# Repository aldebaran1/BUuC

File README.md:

This repo holds files for BU Arduino

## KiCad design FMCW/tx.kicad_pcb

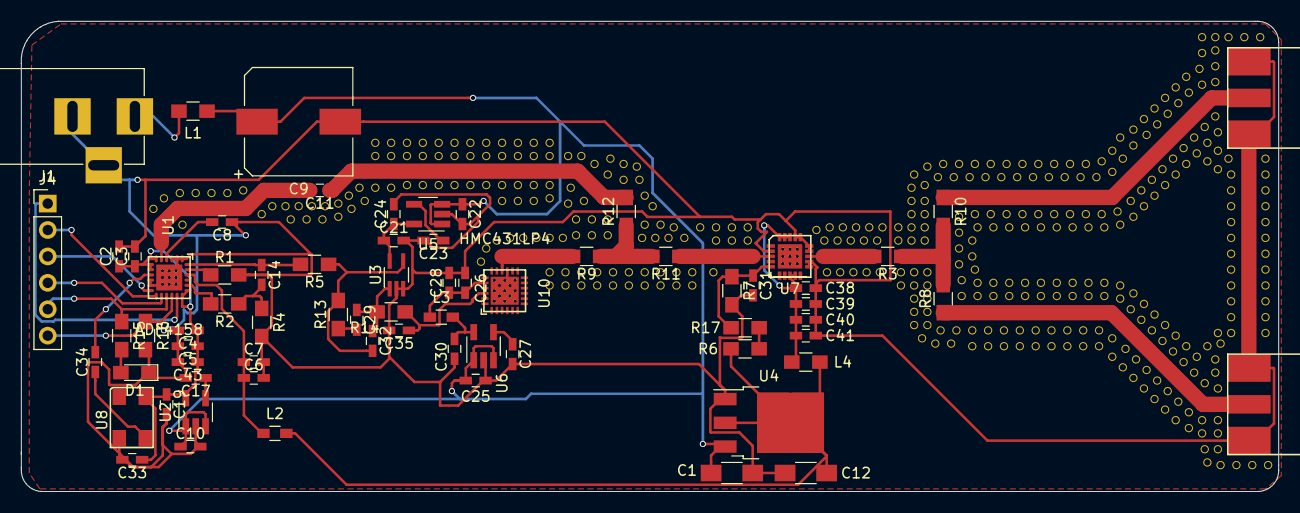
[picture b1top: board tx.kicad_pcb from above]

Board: 2 copper layers, 120.9 x 45.2 mm, 70 parts (0 on the bottom side), 42 nets.

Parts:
C1: 10u; C_1206_HandSoldering
C2, C4, C6, C21, C33, C34, C43: 100n; C_0603_HandSoldering
C3, C5, C7: 10p; C_0603_HandSoldering
C8, C11, C40, C41: 100p; C_0603_HandSoldering
C9: 470u; CP_Elec_10x10
C10, C22, C25: 1u; C_0603_HandSoldering
C12: 100u; C_1206_HandSoldering
C14: 47p; C_0603_HandSoldering
C17, C23, C27, C28, C31: 10n; C_0603_HandSoldering
C19, C26, C30: 4.7u; C_0603_HandSoldering
C24, C39: 2.2u; C_0603_HandSoldering
C29: 20n; C_0603_HandSoldering
C32: 750p; C_0603_HandSoldering
C35: 56n; C_0603_HandSoldering
C38: 10u; C_0603_HandSoldering
D1: LED; LED_0805_HandSoldering
J1: Barrel_Jack; BARREL_JACK
J2: SMA_RX; SMA_molex_straight
J3: SMA_TX; SMA_molex_straight
J4: Conn_01x06_Male; Pin_Header_Straight_1x06_Pitch2.54mm
L1, L4: CIC21P101NE; L_0805_HandSoldering
L2, L3: BLM18PG181SN1D; L_0603_HandSoldering
R1, R7: 5.1k; R_0805_HandSoldering
R2: 1.02k; R_0805_HandSoldering
R3, R8, R9, R10, R11, R12: 16; R_0805_HandSoldering
R4: 3.1k; R_0805_HandSoldering
R5, R15: 1k; R_0805_HandSoldering
R6: 3.3k; R_0805_HandSoldering
R13: 220; R_0805_HandSoldering
R14: 10; R_0805_HandSoldering
R16: 10k; R_0805_HandSoldering
R17: 510; R_0805_HandSoldering
U1: ADF4158; VFQFN-24
U2: LP2985-3.3; SOT-23-5_HandSoldering
U3: TLV172DCK; SOT-353_SC-70-5_Handsoldering
U4: LM1117-5.0; TO-252-3_TabPin2
U5: LP2985-10.0; SOT-23-5_HandSoldering
U6: LP2985-3.0; SOT-23-5_HandSoldering
U7: SE5003_1; SE5003
U8: TCXO
U10: HMC431LP4; VQFN-24

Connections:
/3V0: C30.1, L3.2, U6.5
/3V3: C2.1, C3.1, C4.1, C5.1, C19.1, C33.1, C43.1, U1.6, U1.7, U1.8, U1.18, U1.19, U2.5, U8.4
/5V: C12.1, L2.2, L4.2, R6.2, U4.2
/10V: C21.1, C24.1, U3.5, U5.5
/12V: C1.1, C9.1, C10.1, C22.1, C25.1, L1.1, U2.1, U2.3, U4.3, U5.1, U5.3, U6.1, U6.3
GND: C1.2, C2.2, C3.2, C4.2, C5.2, C6.2, C7.2, C8.1, C9.2, C10.2, C12.2, C17.2, C19.2, C21.2, C22.2, C23.2, C24.2, C25.2, C26.2, C27.2, C28.2, C30.2, C31.2, C33.2, C35.2, C38.1, C39.1, C40.1, C41.1, C43.2, D1.1, J1.2, J1.3, J2.2, J3.2, R1.2, R4.2, R7.2, R16.2, U1.1, U1.2, U1.3, U1.10, U1.11, U1.PAD, U2.2, U3.2, U3.3, U4.1, U5.2, U6.2, U7.2, U7.4, U7.11, U7.12, U7.14, U7.15, U7.16, U7.17, U7.GND, U7.PAD, U8.2, U10.15, U10.PAD
unnamed: C6.1, C7.1, L2.1, U1.22
unnamed: C8.2, U1.4
unnamed: C11.1, R12.2
unnamed: C11.2, U1.5
unnamed: C14.1, R5.2, U1.24
unnamed: C14.2, R2.1, R4.1
unnamed: C17.1, U2.4
unnamed: C23.1, U5.4
unnamed: C26.1, C28.1, L3.1, U10.20
unnamed: C27.1, U6.4
unnamed: C29.1, C32.1, R14.2, U3.1
unnamed: C29.2, R13.1
unnamed: C31.1, R7.1, R17.1, U7.5
unnamed: C32.2, R5.1, R13.2, U3.4
unnamed: C34.1, U8.3
unnamed: C34.2, U1.9
unnamed: C35.1, R14.1, U10.22
unnamed: C38.2, C39.2, C40.2, C41.2, L4.1, U7.8, U7.9, U7.18, U7.19, U7.20
unnamed: D1.2, R15.2
unnamed: J1.1, L1.2
unnamed: J2.1, R10.1
unnamed: J3.1, R8.1
unnamed: J4.1, U1.17
unnamed: J4.2, U1.13
unnamed: J4.3, U1.12
unnamed: J4.4, U1.14
unnamed: J4.5, R15.1, U1.15
unnamed: J4.6, R16.1, U1.16
unnamed: R1.1, U1.23
unnamed: R2.2, U1.20
unnamed: R3.2, U7.13
unnamed: R9.2, U10.16
unnamed: R3.1, R8.2, R10.2
unnamed: R11.1, U7.3
unnamed: R9.1, R11.2, R12.1
unnamed: R6.1, R17.2

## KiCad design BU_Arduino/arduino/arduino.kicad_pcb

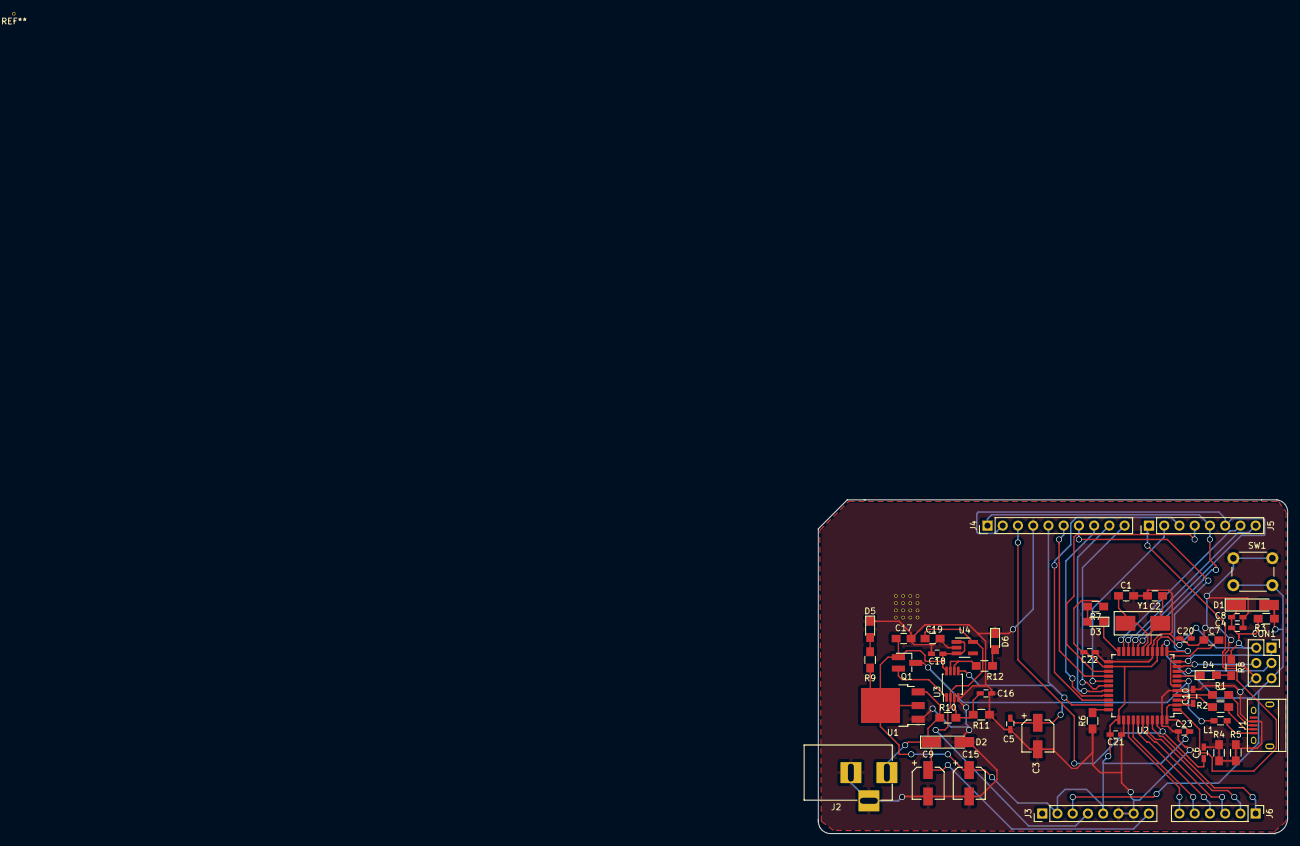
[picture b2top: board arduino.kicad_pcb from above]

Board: 2 copper layers, 78.2 x 55.6 mm, 52 parts (0 on the bottom side), 48 nets.

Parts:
C1, C2: 22pF; C_0805_HandSoldering
C3, C9, C15: 10uF; CP_Elec_5x5.3
C4, C5, C6, C8, C10, C16, C18, C20, C21, C22, C23: 100nF; C_0603_HandSoldering
C7, C17, C19: 1uF; C_0805_HandSoldering
CON1: ICSP; Socket_Strip_Straight_2x03_Pitch2.54mm
D1, D2: D; D_MiniMELF_Handsoldering
D3: TX; LED_0805_HandSoldering
D4: RX; LED_0805_HandSoldering
D5: ON; LED_0805_HandSoldering
D6: L; LED_0805_HandSoldering
J1: USB_A; USB_Micro-B
J2: Barrel_Jack; BARREL_JACK
J3: Power; Socket_Strip_Straight_1x08_Pitch2.54mm
J4: Digital; Socket_Strip_Straight_1x10_Pitch2.54mm
J5: Digital; Socket_Strip_Straight_1x08_Pitch2.54mm
J6: Analog; Socket_Strip_Straight_1x06_Pitch2.54mm
L1: Ferrite_Bead; L_0603_HandSoldering
Q1: FDN340P; SuperSOT-3
R1, R2: 22; R_0805_HandSoldering
R3, R6, R10, R11: 10K; R_0805_HandSoldering
R4, R5: R; R_0805_HandSoldering
R7, R8, R9, R12: 1K; R_0805_HandSoldering
SW1: SW_Push_Dual; SW_PUSH_6mm_h4.3mm
U1: NCP1117-12_TO252; TO-252-3_TabPin2
U2: ATMEGA32U4-AU; TQFP-44_10x10mm_Pitch0.8mm
U3: LMV358; MSOP-8_3x3mm_Pitch0.65mm
U4: LP2985-3.3; SOT-23-5
Y1: 16MHz; Crystal_SMD_0603-2pin_6.0x3.5mm_HandSoldering

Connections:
+3V3: C19.2, J3.4, U3.2, U4.5
+5V: C4.1, C8.1, C10.1, C15.1, C17.1, C18.1, C20.2, C21.2, C22.2, C23.2, CON1.2, D1.1, J3.2, J3.5, Q1.1, R3.1, R7.1, R8.1, R9.1, U1.2, U2.2, U2.14, U2.24, U2.34, U2.44, U3.8, U4.1, U4.3
/A0: J6.6, U2.36
/A1: J6.5, U2.37
/A2: J6.4, U2.38
/A3: J6.3, U2.39
/A4: J6.2, U2.40
/A5: J6.1, U2.41
/AREF: C6.1, J4.3, U2.42
/D0/RX: J5.8, U2.20
/D1/TX: J5.7, U2.21
/D2/SDA: J4.2, J5.6, U2.19
/D3/SCL: J4.1, J5.5, U2.18
/D4: J5.4, U2.25
/D5: J5.3, U2.31
/D6: J5.2, U2.27
/D7: J5.1, U2.1
/HWB: R6.2, U2.33
/IO8: J4.10, U2.28
/IO9: J4.9, U2.29
/IO10: J4.8, U2.30
/IO11: J4.7, U2.12
/IO12: J4.6, U2.26
/IO13: J4.5, U2.32, U3.5
/MISO: CON1.1, U2.11
/MOSI: CON1.4, U2.10
/RST: CON1.5, D1.2, J3.3, R3.2, SW1.1, U2.13
/RXLED: D4.1, U2.8
/SCK: CON1.3, U2.9
/TXLED: D3.1, U2.22
/VIN: C9.1, D2.1, J2.1, J3.8, R10.1, U1.3
/VUSB: C3.1, C5.1, L1.1, Q1.3, U2.7
GND: C1.2, C2.2, C3.2, C4.2, C5.2, C6.2, C7.1, C8.2, C9.2, C10.2, C15.2, C16.2, C17.2, C18.2, C19.1, C20.1, C21.1, C22.1, C23.1, CON1.6, D2.2, D5.1, D6.1, J1.4, J2.2, J2.3, J3.6, J3.7, J4.4, R4.1, R4.2, R5.1, R5.2, R6.1, R11.2, SW1.2, U1.1, U2.5, U2.15, U2.23, U2.35, U2.43, U3.4, U4.2
unnamed: C1.1, U2.17, Y1.1
unnamed: C2.1, U2.16, Y1.2
unnamed: C7.2, U2.6
unnamed: C16.1, R10.2, R11.1, U3.3
unnamed: D3.2, R7.2
unnamed: D4.2, R8.2
unnamed: D5.2, R9.2
unnamed: D6.2, R12.2
unnamed: J1.1, L1.2
unnamed: J1.2, R2.2
unnamed: J1.3, R1.2
unnamed: Q1.2, U3.1
unnamed: R1.1, U2.4
unnamed: R2.1, U2.3
unnamed: R12.1, U3.6, U3.7

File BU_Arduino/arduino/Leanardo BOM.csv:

Source:,/Users/Rahul/Documents/KiCAD/circuit/arduino/arduino.sch,,
Date:,"Thursday, June 21, 2018 'PMt' 03:21:46 PM",,
Tool:,Eeschema 4.0.7,,
Component Count:,52,,
Ref,Value,Footprint,Link
C1,22pF,Capacitors_SMD:C_0805_HandSoldering,https://www.digikey.com/product-detail/en/wurth-electronics-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
C2,22pF,Capacitors_SMD:C_0805_HandSoldering,https://www.digikey.com/product-detail/en/wurth-electronics-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
C3,10uF,Capacitors_SMD:CP_Elec_5x5.3,https://www.digikey.com/product-detail/en/wurth-electronics-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
C4,100nF,Capacitors_SMD:C_0805_HandSoldering,https://www.digikey.com/product-detail/en/vishay-vitramon/VJ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
C5,100nF,Capacitors_SMD:C_0805_HandSoldering,https://www.digikey.com/product-detail/en/vishay-vitramon/VJ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
C6,100nF,Capacitors_SMD:C_0805_HandSoldering,https://www.digikey.com/product-detail/en/vishay-vitramon/VJ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
C7,1uF,Capacitors_SMD:C_0805_HandSoldering,https://www.digikey.com/product-detail/en/murata-electronics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
C8,100nF,Capacitors_SMD:C_0805_HandSoldering,https://www.digikey.com/product-detail/en/vishay-vitramon/VJ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
C9,10uF,Capacitors_SMD:CP_Elec_5x5.3,https://www.digikey.com/product-detail/en/wurth-electronics-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
C10,100nF,Capacitors_SMD:C_0603_HandSoldering,https://www.digikey.es/product-detail/en/kemet/C0603C103K4RA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
C15,10uF,Capacitors_SMD:CP_Elec_5x5.3,https://www.digikey.com/product-detail/en/wurth-electronics-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
C16,100nF,Capacitors_SMD:C_0805_HandSoldering,https://www.digikey.com/product-detail/en/vishay-vitramon/VJ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
C17,1uF,Capacitors_SMD:C_0805_HandSoldering,https://www.digikey.com/product-detail/en/murata-electronics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
C18,100nF,Capacitors_SMD:C_0805_HandSoldering,https://www.digikey.com/product-detail/en/vishay-vitramon/VJ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
C19,1uF,Capacitors_SMD:C_0805_HandSoldering,https://www.digikey.com/product-detail/en/murata-electronics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
C20,100nF,Capacitors_SMD:C_0603_HandSoldering,https://www.digikey.es/product-detail/en/kemet/C0603C103K4RA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
C21,100nF,Capacitors_SMD:C_0603_HandSoldering,https://www.digikey.es/product-detail/en/kemet/C0603C103K4RA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
C22,100nF,Capacitors_SMD:C_0603_HandSoldering,https://www.digikey.es/product-detail/en/kemet/C0603C103K4RA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
C23,100nF,Capacitors_SMD:C_0603_HandSoldering,https://www.digikey.es/product-detail/en/kemet/C0603C103K4RA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
CON1,ICSP,Buttons_Switches_SMD:SW_DIP_x3_W8.61mm_Slide_LowProfile,
D1,D,Diodes_SMD:D_MiniMELF_Handsoldering,https://www.digikey.com/product-detail/en/on-semiconductor/L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
D2,D,Diodes_SMD:D_MiniMELF_Handsoldering,https://www.digikey.com/product-detail/en/on-semiconductor/L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
D3,TX,LEDs:LED_0805_HandSoldering,https://www.digikey.com/product-detail/en/lite-on-inc/LTST-C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
D4,RX,LEDs:LED_0805_HandSoldering,https://www.digikey.com/product-detail/en/lite-on-inc/LTST-C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
D5,ON,LEDs:LED_0805_HandSoldering,https://www.digikey.com/product-detail/en/lite-on-inc/LTST-C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
D6,L,LEDs:LED_0805_HandSoldering,https://www.digikey.com/product-detail/en/lite-on-inc/LTST-C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
J1,USB_A,Connectors:USB_Micro-B,https://www.digikey.com/product-detail/en/amphenol-fci/10118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
J2,Barrel_Jack,Connectors:BARREL_JACK,https://www.digikey.com/product-detail/en/cui-inc/PJ-002B/CP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
J3,Power,Socket_Strips:Socket_Strip_Straight_1x08_Pitch2.54mm,
J4,Digital,Socket_Strips:Socket_Strip_Straight_1x10_Pitch2.54mm,
J5,Digital,Socket_Strips:Socket_Strip_Straight_1x08_Pitch2.54mm,
J6,Analog,Socket_Strips:Socket_Strip_Straight_1x06_Pitch2.54mm,
L1,Ferrite_Bead,Inductors_SMD:L_0603_HandSoldering,https://www.digikey.com/product-detail/en/murata-electronics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
Q1,FDN340P,TO_SOT_Packages_SMD:SuperSOT-3,https://www.digikey.com/product-detail/en/on-semiconductor/F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
R1,22,Resistors_SMD:R_0805_HandSoldering,https://www.digikey.com/product-detail/en/susumu/RR1220Q-220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
R2,22,Resistors_SMD:R_0805_HandSoldering,https://www.digikey.com/product-detail/en/susumu/RR1220Q-220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
R3,10K,Resistors_SMD:R_0805_HandSoldering,https://www.digikey.com/product-detail/en/susumu/RR1220P-103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
R4,R,Resistors_SMD:R_0805_HandSoldering,
R5,R,Resistors_SMD:R_0805_HandSoldering,
R6,10K,Resistors_SMD:R_0805_HandSoldering,https://www.digikey.com/product-detail/en/susumu/RR1220P-103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
R7,1K,Resistors_SMD:R_0805_HandSoldering,https://www.digikey.com/product-detail/en/susumu/RR1220P-102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
R8,1K,Resistors_SMD:R_0805_HandSoldering,https://www.digikey.com/product-detail/en/susumu/RR1220P-102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
R9,1K,Resistors_SMD:R_0805_HandSoldering,https://www.digikey.com/product-detail/en/susumu/RR1220P-102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
R10,10K,Resistors_SMD:R_0805_HandSoldering,https://www.digikey.com/product-detail/en/susumu/RR1220P-103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
R11,10K,Resistors_SMD:R_0805_HandSoldering,https://www.digikey.com/product-detail/en/susumu/RR1220P-103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
R12,1K,Resistors_SMD:R_0805_HandSoldering,https://www.digikey.com/product-detail/en/susumu/RR1220P-102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
SW1,SW_Push_Dual,Buttons_Switches_THT:SW_PUSH_6mm_h4.3mm,https://www.digikey.com/product-detail/en/cw-industries/GPTS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
U1,NCP1117-12_TO252,TO_SOT_Packages_SMD:TO-252-2,https://www.digikey.com/product-detail/en/on-semiconductor/N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
U2,ATMEGA32U4-AU,Housings_QFP:TQFP-44_10x10mm_Pitch0.8mm,https://www.digikey.com/product-detail/en/microchip-technolo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
U3,LMV358,Housings_SSOP:MSOP-8_3x3mm_Pitch0.65mm,https://www.digikey.com/product-detail/en/texas-instruments/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
U4,LP2985-3.3,TO_SOT_Packages_SMD:SOT-23-5,https://www.digikey.com/product-detail/en/texas-instruments/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
Y1,16MHz,Crystals:Crystal_SMD_0603-2pin_6.0x3.5mm_HandSoldering,https://www.digikey.com/product-detail/en/abracon-llc/ABLS-1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

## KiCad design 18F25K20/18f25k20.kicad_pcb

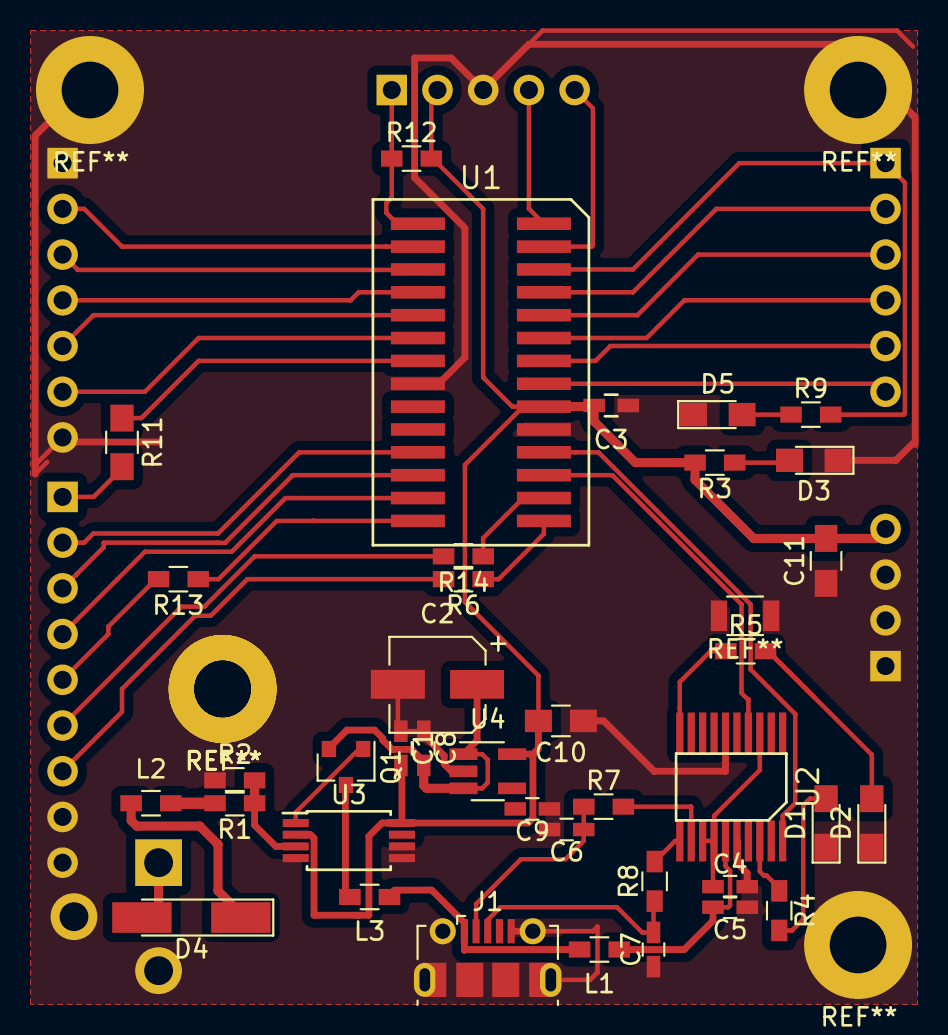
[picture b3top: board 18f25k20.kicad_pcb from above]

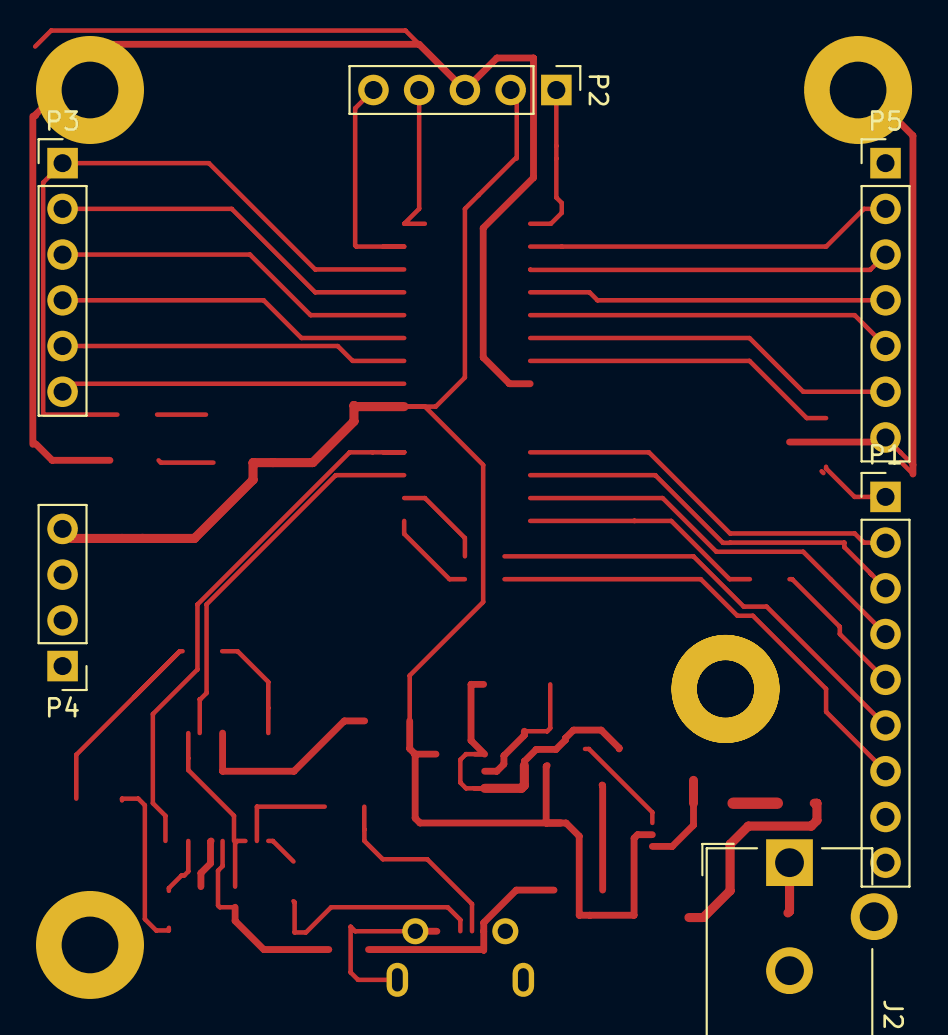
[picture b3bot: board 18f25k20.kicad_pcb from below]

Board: 2 copper layers, 44 parts (6 on the bottom side), 50 nets.

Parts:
C1, C3, C4, C5: 100n; C_0603_HandSoldering
C2: 10u; CP_Elec_5x5.3
C6, C7: 47p; C_0603_HandSoldering
C8: 1u; C_0603_HandSoldering
C9: 10n; C_0603_HandSoldering
C10, C11: 4u7; C_0805_HandSoldering
D1, D2, D3, D5: LED; LED_0805_HandSoldering
D4: LL4148; D_MiniMELF_Handsoldering
J1: USB_OTG; USB_Micro-B_Molex-105017-0001
J2: Barrel_Jack; Barrel_Jack_CUI_PJ-102AH
L1, L2, L3: FB; L_0603_HandSoldering
P1: SPI; Pin_Header_Straight_1x09_Pitch2.54mm
P2: ICSP; Pin_Header_Straight_1x05_Pitch2.54mm
P3: PORTB; Pin_Header_Straight_1x06_Pitch2.54mm
P4: power supply; Pin_Header_Straight_1x04_Pitch2.54mm
P5: ADC; Pin_Header_Straight_1x07_Pitch2.54mm
Q1: FDN240P; SOT-23
R1, R2, R12: 10k; R_0603_HandSoldering
R3, R4, R5, R9: 270R; R_0603_HandSoldering
R6, R13, R14: 220R; R_0603_HandSoldering
R7, R8: 27R; R_0603_HandSoldering
R11: 0R; R_0805_HandSoldering
U1: 18F25K20_ssop; SSOP-28_hand_solder
U2: FTDI231x; SSOP-20_FTD23x
U3: LM358; TSSOP-8_4.4x3mm_Pitch0.65mm
U4: LP2985-3.3; SOT-23-5_HandSoldering

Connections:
/D+: R8.2, U2.11
/D-: R7.2, U2.12
/RC0: P1.2, U1.11
/RC1: P1.3, U1.12
/RC2: P1.4, U1.13
/RXD: U1.17, U2.4
/Rx_led: R4.1, U2.18
/SCK: P1.5, R13.2
/SDI: P1.7, R6.2
/SDO: P1.6, R14.2
/SS: P1.1, R11.2
/TXD: U1.18, U2.20
/Tx_led: R5.1, U2.10
/Vin: C2.1, C8.2, Q1.2, U4.1, U4.3
/Vin_cmp: R1.1, R2.2, U3.3
/Vusb: L3.2, Q1.3
/gate_cmd: Q1.1, U3.1
/picled: P3.1, R9.2, U1.26
/ps: L2.2, R1.2
GND: C1.1, C2.2, C3.1, C4.2, C5.1, C6.2, C7.1, C8.1, C9.1, C10.1, C11.1, D1.1, D2.1, D3.1, D5.1, J1.5, J1.6, J2.2, J2.3, P1.8, P1.9, P2.3, P4.1, P4.2, P4.3, P5.1, P5.7, R2.1, U1.8, U1.19, U2.6, U2.16, U3.4, U3.5, U3.6, U4.2
unnamed: C4.1, U2.3, U2.13, U2.14
unnamed: C5.2, L1.1, U2.15
unnamed: C6.1, J1.2, R7.1
unnamed: C7.2, J1.3, R8.1
unnamed: C9.2, U4.4
unnamed: D1.2, R4.2
unnamed: D2.2, R5.2
unnamed: D3.2, R3.1
unnamed: D4.1, L2.1
unnamed: D4.2, J2.1
unnamed: D5.2, R9.1
unnamed: J1.1, L1.2, L3.1
unnamed: P2.1, R12.1, U1.1
unnamed: P2.4, U1.28
unnamed: P2.5, U1.27
unnamed: P3.2, U1.25
unnamed: P3.3, U1.24
unnamed: P3.4, U1.23
unnamed: P3.5, U1.22
unnamed: P3.6, U1.21
unnamed: P5.2, U1.2
unnamed: P5.3, U1.3
unnamed: P5.4, U1.4
unnamed: P5.5, U1.5
unnamed: P5.6, U1.6
unnamed: R6.1, U1.15
unnamed: R11.1, U1.7
unnamed: R13.1, U1.14
unnamed: R14.1, U1.16
VCC: C1.2, C3.2, C10.2, C11.2, P2.2, P4.4, R3.2, R12.2, U1.20, U3.2, U3.8, U4.5

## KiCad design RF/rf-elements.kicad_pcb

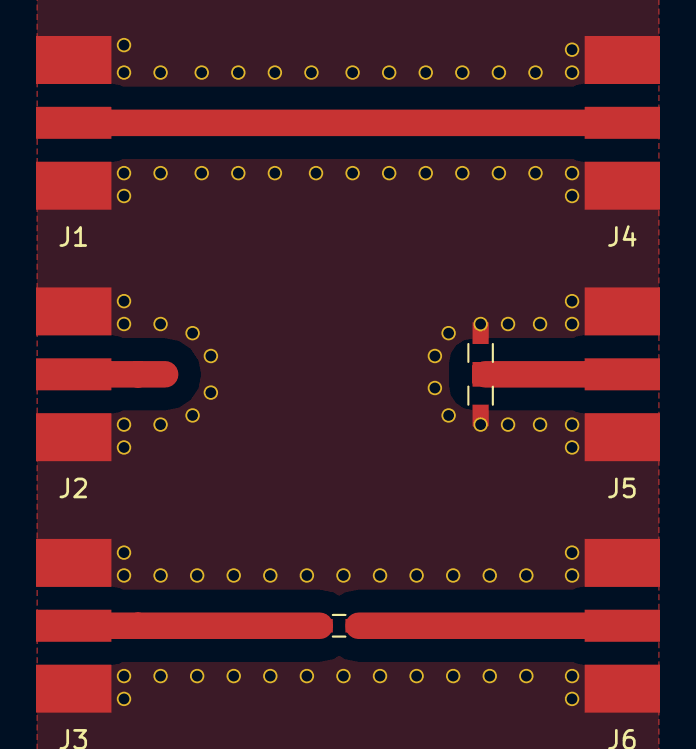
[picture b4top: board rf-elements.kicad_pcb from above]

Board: 2 copper layers, 9 parts (0 on the bottom side), 5 nets.

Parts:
C1: 47p; C_0603
J1, J2, J3, J4, J5, J6: Conn_Coaxial; SMA_molex_straight
R1, R2: 100R; R_0603_HandSoldering

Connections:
GND: J1.2, J2.2, J3.2, J4.2, J5.2, J6.2, R1.1, R2.1
unnamed: C1.1, J6.1
unnamed: C1.2, J3.1
unnamed: J1.1, J4.1
unnamed: J5.1, R1.2, R2.2

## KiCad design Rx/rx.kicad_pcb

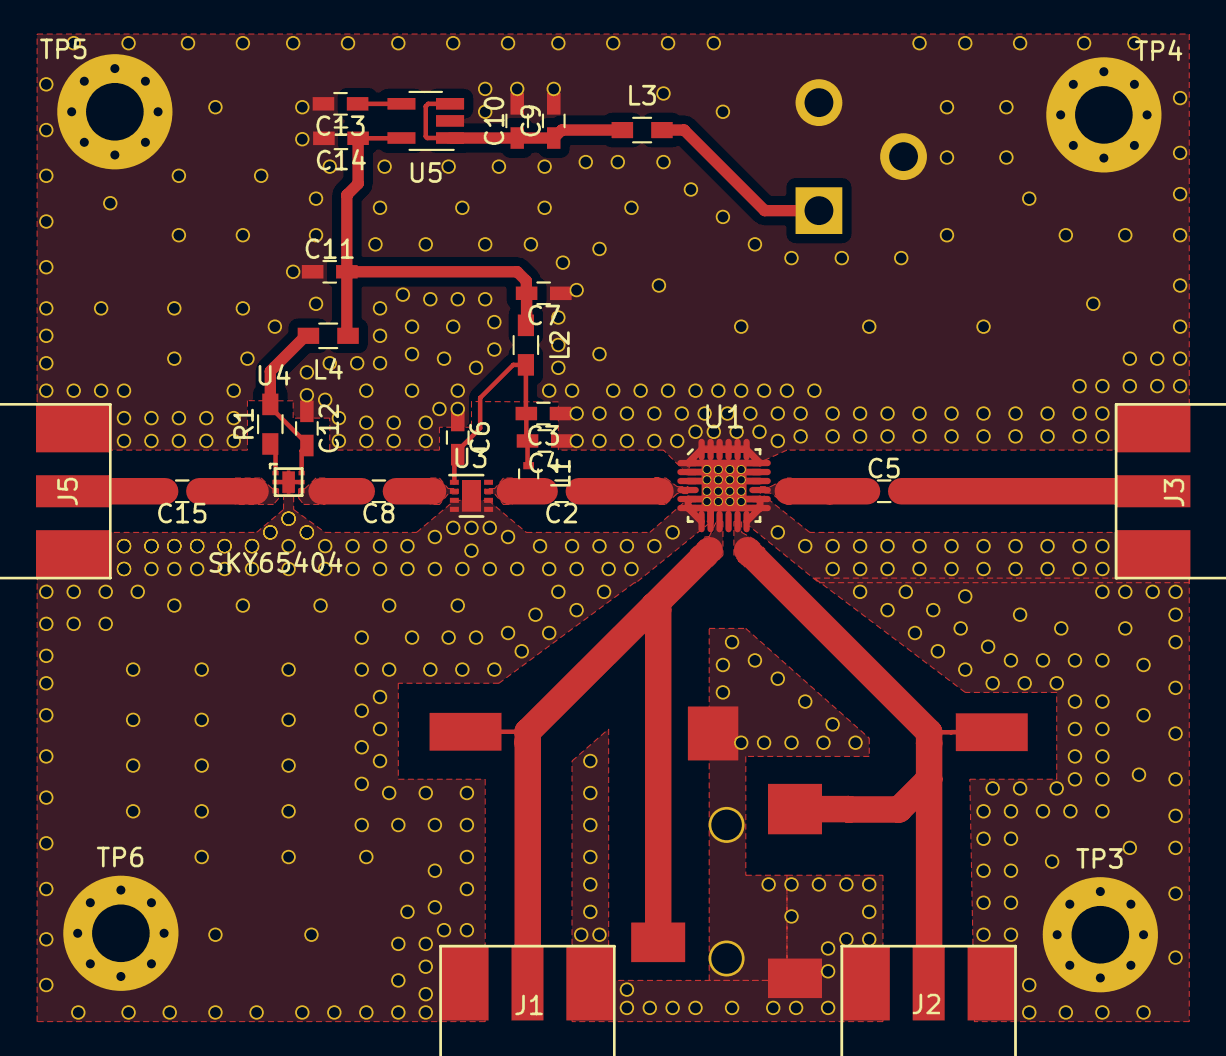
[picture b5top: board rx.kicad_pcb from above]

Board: 2 copper layers, 35 parts (1 on the bottom side), 18 nets.

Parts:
C2, C5, C8, C15: 18p; C_0603_HandSoldering
C3, C13: 10n; C_0603_HandSoldering
C4: 10p; C_0603_HandSoldering
C6, C12: 100n; C_0603_HandSoldering
C7, C10, C11: 1u; C_0603_HandSoldering
C9, C14: 4u7; C_0603_HandSoldering
J1, J2, J3, J5: sma; SMA_molex_straight
J4: Barrel_Jack; Barrel_Jack_CUI_PJ-102AH
L1: 3n9; L_0402
L2, L3, L4: FB; L_0603_HandSoldering
R1: 100R; R_0603_HandSoldering
TP1, TP2: TEST; TP
TP3, TP4, TP5, TP6: TEST; MountingHole_3.2mm_M3_Pad_Via_mod
U1: HMC525; HMC525_QFP24
U2: Audio-jack-4pin; Headphone_jack_pcb
U3: TRF37A75; DFN-8-1EP_2x2mm_Pitch0.5mm
U4: SKY65404; XFDFN-6
U5: LP2985-3.3; SOT-23-5_HandSoldering

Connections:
GND: C3.1, C4.1, C6.1, C7.1, C9.2, C10.2, C11.1, C12.1, C13.2, C14.2, J1.2, J2.2, J3.2, J4.2, J4.3, J5.2, TP3.1, TP4.1, TP5.1, TP6.1, U1.1, U1.2, U1.3, U1.5, U1.6, U1.7, U1.8, U1.10, U1.12, U1.13, U1.14, U1.16, U1.17, U1.18, U1.19, U1.20, U1.21, U1.22, U1.23, U1.24, U1.EP, U2.1, U2.4, U3.3, U3.4, U3.5, U3.6, U3.8, U3.9, U4.2, U4.5, U4.PAD, U5.2
unnamed: C2.1, U1.4
unnamed: C2.2, L1.2, U3.7
unnamed: C3.2, C4.2, C6.2, L1.1, L2.2, U3.1
unnamed: C5.1, U1.15
unnamed: C5.2, J3.1
unnamed: C8.1, U3.2
unnamed: C8.2, U4.4
unnamed: C9.1, C10.1, L3.1, U5.1, U5.3
unnamed: C12.2, L4.2, R1.2, U4.6
unnamed: C13.1, U5.4
unnamed: C15.1, U4.3
unnamed: C15.2, J5.1
unnamed: J1.1, TP1.1, U1.9, U2.3
unnamed: J2.1, TP2.1, U1.11, U2.2
unnamed: J4.1, L3.2
unnamed: R1.1, U4.1
VCC: C7.2, C11.2, C14.1, L2.1, L4.1, U5.5

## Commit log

2018-06-23 Initial PIC 18F2520 QFN
2018-07-11 added readme file
2018-07-11 Added BU Arduino Kicad Files
2018-07-11 Added arduino.pretty to arduino folder
2018-07-25 Updated PCB Design Files
2018-07-26 Uploaded FMCW Files
2018-07-26 Uploaded BOM Files
2018-07-26 Uploaded CSV File
2018-07-26 Uploaded CSV Files
2018-07-29 Updated few files
2018-07-31 Uploaded .pretty files
2018-07-31 Uploaded Lib Files
2018-08-01 Updated Files
2018-08-04 PIC-ssop, sch &layout. TODO:modify pinheader+gnd polygon. 3.2mm holes
2018-08-05 RF-test circuit
2018-08-05 layout&vias
2018-08-07 MIxer layout with vias
2018-08-07 Links to parts
2018-08-07 removed duplicated libs
2018-08-07 Layout gap between lines increased
2018-08-07 Moved all footprints to buradar
2018-08-08 Updated Power Supply and Low pass filter
2018-08-08 Added SimPLL Screenshots and Design
2018-08-13 Added gnd planes stiching Vias
2018-08-13 Updated BOM File
2018-08-14 Updated BOM
2018-08-14 Made changes to the capacitors
2018-08-27 Updated pcb files
2018-08-28 Updated pcb with vias
